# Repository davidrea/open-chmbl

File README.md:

# open-chmbl

In automotive engineering, the CHMBL is the "Center High-Mounted Brake Light" — this
repository is an **"Open-sourCe Helmet Mounted Brake Light"** for motorcyclists.

A battery-powered ~8″ LED bar worn on the rider's back — magnetically clamped to a
jacket or backpack — lights up when the motorcycle is braking. The reference bike
doesn't publish a brake-switch bit on its **CAN bus**, so braking is **inferred from
wheel-speed deceleration** read off the bus (via the Euro 5 diagnostic port,
**listen-only**) and sent wirelessly to the rider-side unit over **ESP-NOW**. Clutch
and gear/neutral context lets it hold the light through a stop and release it sensibly
when the bike pulls away — deriving deceleration from the bike's own CAN wheel-speed
(not an accelerometer) keeps it clear of the inertial-detection patents.

Two units, both ESP32-based:

- **[`transmitter/`](transmitter)** — bike-side; plugs into the diagnostic port,
  decodes CAN, broadcasts braking state.
- **[`brake_light/`](brake_light)** — rider-side; battery-powered LED bar (fabric
  mount this rev; helmet fitment deferred) that renders the state.

> ⚠️ Auxiliary device. It does **not** replace the bike's factory brake light, and
> helmet-mounted lighting is restricted in some places. Read
> **[`docs/safety-regulatory.md`](docs/safety-regulatory.md)** before building or
> riding.

## Start here

- **[`ARCHITECTURE.md`](ARCHITECTURE.md)** — system overview and design index.
- **[`docs/feature-functions.md`](docs/feature-functions.md)** — per-device capabilities.
- **[`docs/design/README.md`](docs/design/README.md)** — how we build it: design
  elements, implemented one at a time in isolation.
- [`docs/cli.md`](docs/cli.md) · [`docs/hardware.md`](docs/hardware.md) ·
  [`docs/firmware.md`](docs/firmware.md) · [`docs/protocol.md`](docs/protocol.md) ·
  [`docs/can-profiles.md`](docs/can-profiles.md) ·
  [`docs/safety-regulatory.md`](docs/safety-regulatory.md) ·
  [`docs/roadmap.md`](docs/roadmap.md)

Status: **architecture / design phase** (see the roadmap).

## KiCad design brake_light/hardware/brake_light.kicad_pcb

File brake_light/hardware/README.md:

# Brake_light — hardware

Rider-side electronics. See [`docs/hardware.md §2`](../../docs/hardware.md#2-brake_light-rider-side)
for the block diagram and parts sketch.

Key constraints:
- **Bare ESP32-C3 module** (ESP32-C3-WROOM-02 baseline) + **chip-down** LiIon
  charger, DC-DC, and LED driver. Moved off the integrated dev-board path (previously
  scoped in the removed `§2.1` module survey) to unlock the thin/wide form factor
  below — see [`docs/hardware.md §2.1`](../../docs/hardware.md#21-parts-direction-bare-module--chip-down).
- **~8″ wide red LED bar** (620–630 nm mid-power) driven from a boost constant-current
  driver. Series-string + boost topology set in
  [`docs/design/de-04`](../../docs/design/de-04-led-render.md), which down-selected the
  TI **LM3410**; the **first pass fitted two `AP3019AKTR` drivers** on the §3.1
  two-parallel-strings branch — see
  [the as-built summary below](#as-built-block-summary-first-pass-schematic) and
  [DE-04 §3.5](../../docs/design/de-04-led-render.md).
- **Binary on/off bar — brightness deferred.** The firmware drives each driver's
  `CTRL`/`EN` pin as a **static enable**, and the LED current is fixed by the sense
  resistors. No PWM dimming, no ambient auto-dimming for now; the decision is recorded
  in [`docs/design/de-04`](../../docs/design/de-04-led-render.md), the deferred element
  is [`de-02`](../../docs/design/de-02-auto-brightness.md). The ambient-light sensor is
  **fitted but unused**, so this is a firmware-only change later. Auto-dimming remains a
  safety requirement (no blinding at night) — deferred, not dropped.
- **Status-indicator LEDs** — **separate from the bar** for status/fault reporting
  ([`docs/design/de-10`](../../docs/design/de-10-status-indicator.md)). DE-10 specified a
  chip-down WS2812B; the **first pass fitted two discrete mono LEDs (D13 RED / D14 GRN)**
  instead, which loses the full RGB code space — see
  [DE-10 §3](../../docs/design/de-10-status-indicator.md).
- **Battery: 1S 18650 Li-ion, protected cell** + USB-C charging. 18650 chosen over
  pouch/LiPo because pouch cells need mechanical compression the thin enclosure can't
  provide; a protected cell means the charge IC doesn't have to double as cell
  protection. The charger baseline was an MCP73871 (load-share); the **first pass fitted
  a `BQ21040DBV`**, so the load-sharing behaviour needs confirming.
- **Form factor: thin, short-in-vertical (viewed from the rear), wide.** The ~8″ LED
  bar sets the width; the 18650's ~18 mm diameter sets the enclosure-thickness floor.
- **Mount: magnetic to jacket / backpack fabric.** Magnets live in the light
  assembly; a thin steel strip or washers sit inside the garment or pack so the
  fabric is sandwiched between them. This is the [garment / backpack shoulder
  mount](../../docs/design/explorations/mounting-magnetic.md#exploration-a--garment--backpack-shoulder-mount)
  exploration promoted to the current baseline; helmet fitment and cross-form
  interchangeability are **deferred**.
- Sized for a full-day runtime target — with a ~3000 mAh 18650 the runtime budget
  roughly doubles the earlier 1500 mAh LiPo worked example (see hardware doc).
- Sealed, IP65+ enclosure.

⚠️ Mounting + Li-ion safety are mandatory reading: [`docs/safety-regulatory.md`](../../docs/safety-regulatory.md).

---

## Status of the design files

| File | State |
|------|-------|
| [`brake_light.kicad_sch`](brake_light.kicad_sch) | **First pass, committed.** Power, charge, buck, USB-C + ESD, MCU, ambient-light sensor and both LED strings are drawn and wired. Four MCU-side nets are **not yet wired** — see [Not yet assigned](#not-yet-assigned-provisional-in-firmware). |
| [`brake_light.kicad_pcb`](brake_light.kicad_pcb) | **First pass, committed.** Carries the netlist generated from the schematic (used to verify the table below). Not yet fabricated or brought up. |
| BOM | To be exported once the unwired nets are resolved. |
| Enclosure / mount files | Still to be added (Phase 4). |

> Nothing here has been built or measured yet. Treat every value below as
> "as-drawn", not "as-measured".

## As-built block summary (first-pass schematic)

| Block | Part | Notes |
|-------|------|-------|
| MCU | **U1 `ESP32-C3-WROOM-02`** | Bare module; native USB on IO18/IO19 |
| Brake bar, string A | **U3 `AP3019AKTR`** boost CC driver | L1 22 µH, C4 0.22 µF out, **R4 560 mΩ** sense; drives **D3…D12 (10 emitters)** in series |
| Brake bar, string B | **U6 `AP3019AKTR`** boost CC driver | L2 22 µH, C7 0.22 µF out, **R10 560 mΩ** sense; drives **D15…D24 (10 emitters)** in series |
| Charger | **U2 `BQ21040DBV`** | From USB VBUS; `TS` ← NTC **TH1**, `ISET` ← R9, `~CHG` → status LED **D2** |
| 3V3 rail | **U7 `TPS62162DSGR`** buck | VBAT → 3V3; `EN` tied to VBAT (always on); `PG` → R14 1 kΩ → the C3's `EN`, so the MCU is held in reset until 3V3 is good |
| Ambient light | **U5 `ISL29035`** | I²C + interrupt. **Populated but unused in firmware** — see [DE-02](../../docs/design/de-02-auto-brightness.md) |
| USB-C | **J2** + **U4 `USBLC6-2P6`** | CC1/CC2 5.1 kΩ (R1/R2), D+/D− ESD-clamped |
| Status LEDs | **D13 (RED)**, **D14 (GRN)** | Each **cathode → GND, anode → 100 Ω (R21 / R20) → MCU pin**, i.e. **active high** |
| Buttons | **SW1 BOOT/USER**, **SW2 RST** | Both switch to GND (active low) |
| Cell | **BT1** 1S Li-ion (18650) | |

**Fixed LED current setpoint.** The sense resistors set the string current in
hardware — there is no firmware dimming (see
[DE-04](../../docs/design/de-04-led-render.md)). The schematic's own sizing note reads
`R = 0.2 V / I_LED`, so **R = 560 mΩ → I_string ≈ 357 mA**, dissipating ≈ 71 mW in the
sense resistor. Ten 620–630 nm emitters at V<sub>f</sub> ≈ 2.1 V put each string at
≈ 21 V, inside the driver's noted 30 V ceiling. The intensity this *should* be is set by
the [LED brightness benchmark](../../docs/led-brightness-benchmark.md) — which is still
the governing sizing study, and which this first pass has **not** been reconciled against
(see the open items below).

---

## Pin map

Derived from the committed design files: the ESP32-C3 pin numbers and the pin↔net
assignments below were read out of **`brake_light.kicad_sch`** and cross-checked against
the net assigned to each pad in **`brake_light.kicad_pcb`** (which KiCad generates from
the schematic). Where the two are quoted together they agree.

### Verified from the netlist

| Function | ESP32-C3 signal | Module pad | How it is wired |
|----------|-----------------|:----------:|-----------------|
| ISL29035 **SDA** | `IO0` | 18 | → U5.6 `SDA`; 4.7 kΩ pull-up (R6) to +3V3 |
| ISL29035 **SCL** | `IO1` | 17 | → U5.5 `SCL`; 4.7 kΩ pull-up (R7) to +3V3 |
| ISL29035 **INT** | `IO3` | 15 | → U5.4 `~INT`; 4.7 kΩ pull-up (R8) to +3V3 |
| **SW1** BOOT/USER button | `IO9` | 8 | → SW1.1; SW1.2 → GND ⇒ **active low**, needs the internal pull-up |
| USB **D−** | `IO18` | 13 | → U4 `I/O1` → J2 `A7`/`B7` |
| USB **D+** | `IO19` | 14 | → U4 `I/O2` → J2 `A6`/`B6` |
| UART **TXD** test point | `IO21` | 12 | → TP1 |
| UART **RXD** test point | `IO20` | 11 | → TP2 |
| Chip **reset** | `EN` | 2 | SW2 (RST) to GND + R5 10 kΩ pull-up + R14 from U7 `PG` |
| Supply | `3V3` / `GND` | 1 / 9, 19 | U7 buck output |

So the ambient-light sensor, the user button, USB and the console test points **are**
fully determined by the committed design files.

### Not yet assigned (provisional in firmware)

These four MCU-side nets are **not wired in the committed first pass** — the board
netlist reports each pad as its own single-pad `unconnected-(…)` net:

| Function | Pad that is open | Netlist name |
|----------|------------------|--------------|
| Brake bar **string A** driver enable | U3 pin 4 `CTRL` | `unconnected-(U3-CTRL-Pad4)` |
| Brake bar **string B** driver enable | U6 pin 4 `CTRL` | `unconnected-(U6-CTRL-Pad4)` |
| Status LED **RED** feed | R21 pin 1 (→ D13 anode) | `unconnected-(R21-Pad1)` |
| Status LED **GRN** feed | R20 pin 1 (→ D14 anode) | `unconnected-(R20-Pad1)` |

Free module GPIOs available for them: `IO2`, `IO4`, `IO5`, `IO6`, `IO7`, `IO8`, `IO10`.

The firmware therefore keeps all four as Kconfig symbols with **provisional defaults**,
so nothing is hard-coded ahead of a schematic review
([`brake_light/software/README.md`](../software/README.md)):

| Function | Provisional default (esp32c3) | Kconfig symbol |
|----------|-------------------------------|----------------|
| String A enable (U3 `CTRL`) | `IO5` | `CHMBL_BAR_EN_A_GPIO` |
| String B enable (U6 `CTRL`) | `IO6` | `CHMBL_BAR_EN_B_GPIO` |
| Status LED RED (D13 via R21) | `IO7` | `CHMBL_STATUS_LED_RED_GPIO` |
| Status LED GRN (D14 via R20) | `IO10` | `CHMBL_STATUS_LED_GRN_GPIO` |

Why those four, if the schematic review wants a starting point:

- **Avoid `IO2` and `IO8`** — both are ESP32-C3 boot **strapping** pins. A driver-enable
  or LED pin sitting low through reset would change the boot mode.
- **`IO9` is taken** by SW1 (and is itself the download-boot strap).
- **Keep `IO4` free.** With `IO0`/`IO1`/`IO3` on the I²C bus and `IO2` strapping, `IO4` is
  the last ADC1-capable pin left, and a battery-sense divider (DE-05) is the obvious next
  thing that needs one — note there is **no battery-voltage sense net on the board yet
  either**.
- `IO4`–`IO7` double as the C3's JTAG pins, which this board does not need: debug goes
  over the native USB Serial/JTAG on `IO18`/`IO19`.

**Active levels.** The status-LED orientation **is** verified (cathode to GND, anode fed
through the 100 Ω resistor), so those pins are **active high**. The AP3019A `CTRL` pin is
also active high, and the firmware drives it as a **static enable** — high = that string
lit at the sense-resistor setpoint, low = dark. That is a deliberate deferral of PWM
dimming, recorded in [DE-04](../../docs/design/de-04-led-render.md).

---

## Open items from this first pass

1. **Wire the four nets above** (both driver `CTRL` pins and both status-LED feeds), then
   fold the agreed GPIO numbers back into this table and the firmware's Kconfig defaults.
2. **Reconcile the LED operating point with the sizing study.** As drawn the bar is
   **2 strings × 10 emitters at ≈ 357 mA each** (≈ 714 mA of LED current). DE-04 §3.4's
   worked baseline is **one string of 8 at ≈ 80 mA**, sized to the
   [benchmark](../../docs/led-brightness-benchmark.md)'s ≈ 50–80 cd daylight target. The
   first-pass board is far above that, which matters more than usual now that brightness
   is fixed in hardware: with dimming deferred there is no firmware knob to pull it back.
   The sense resistors are the only adjustment.
3. **Driver part differs from the DE-04 down-select.** The board uses
   **`AP3019AKTR` ×2**; DE-04 §3.3's trade study concluded **TI LM3410**. The AP3019A's
   higher output ceiling (sheet note "MAX 30V") is what makes the 10-emitter strings
   possible, so this looks like a reasonable substitution — but it has not been run
   through the §3.3 criteria (V<sub>in</sub>-min against the 1S cutoff, switch current,
   EMI next to the 2.4 GHz radio). Confirm against the datasheet and record the outcome in
   DE-04.
4. **No battery-voltage sense and no MCU connection to the charger's `~CHG`** — battery
   state (DE-05) and the charge/low-battery status codes (DE-10) are not observable in
   firmware on this revision.
5. **ISL29035 is populated but unused.** Deliberate: it costs nothing to leave fitted and
   means no hardware change when [DE-02](../../docs/design/de-02-auto-brightness.md) is
   picked back up.

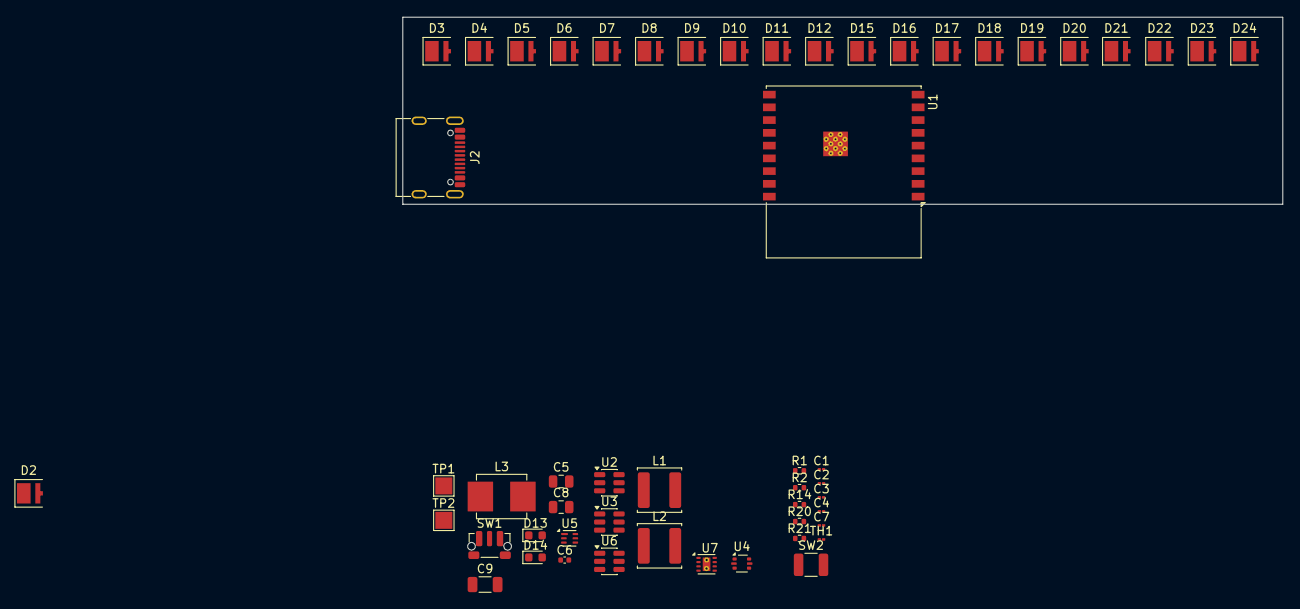
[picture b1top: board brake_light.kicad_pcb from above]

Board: 4 copper layers, 103.5 x 22.0 mm, 53 parts (0 on the bottom side), 45 nets, no tracks yet.

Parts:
C1, C2, C3: 1u; C_01005_0402Metric
C4, C7: 0.22u; C_01005_0402Metric
C5, C8: 10u; C_0805_2012Metric
C6: 100n; C_0402_1005Metric
C9: 22u; C_1206_3216Metric
D2, D3, D4, D5, D6, D7, D8, D9, D10, D11, D12, D15, D16, D17, D18, D19, D20, D21, D22, D23, D24: LED; LED_Luminus_MP-3030-1100_3.0x3.0mm
D13: RED; LED_0603_1608Metric
D14: GRN; LED_0603_1608Metric
J2: USB_C_Receptacle_USB2.0_14P; USB_C_Receptacle_G-Switch_GT-USB-7010ASV
L1, L2: 22u 1.1A; L_Sunlord_SWPA5020S
L3: 2.2u; L_Murata_LQH55DN_5.7x5.0mm
R1, R2: 5.1K; R_0402_1005Metric
R14: 1K; R_0402_1005Metric
R20, R21: 100; R_0402_1005Metric
SW1: BOOT/USER; SW_Push_1P1T-MP_NO_Horizontal_Alps_SKRTLAE010
SW2: RST; R_1210_3225Metric
TH1: Thermistor_NTC; R_01005_0402Metric
TP1: RX; TestPoint_Pad_2.0x2.0mm
TP2: TX; TestPoint_Pad_2.0x2.0mm
U1: ESP32-C3-WROOM-02
U2: BQ21040DBV; SOT-23-6
U3, U6: AP3019AKTR; SOT-23-6
U4: USBLC6-2P6; SOT-666
U5: ISL29035; Renesas_DFN-6_1.5x1.6mm_P0.5mm
U7: TPS62162DSGR; WSON-8-1EP_2x2mm_P0.5mm_EP0.9x1.6mm_ThermalVias

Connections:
+3.3V: C1.1, C5.1, C6.1, C9.1, L3.2, U1.1 (3V3), U5.1 (VDD), U7.6 (VOS)
+5VD: J2.A4 (VBUS), J2.A9 (VBUS), J2.B4 (VBUS), J2.B9 (VBUS), U2.6 (VIN), U4.5 (VBUS)
/DN: J2.A7 (D-), J2.B7 (D-), U1.13 (IO18), U4.1 (I/O1), U4.6 (I/O1)
/DP: J2.A6 (D+), J2.B6 (D+), U1.14 (IO19), U4.3 (I/O2), U4.4 (I/O2)
/EN: R14.1, SW2.1, U1.2 (EN)
/VBAT: C2.1, C3.1, C8.1, L1.2, L2.2, U2.2 (OUT), U3.6 (V_{IN}), U6.6 (V_{IN}), U7.2 (VIN), U7.3 (EN)
GND: C1.2, C2.2, C3.2, C4.2, C5.2, C6.2, C7.2, C8.2, C9.2, D13.1 (K), D14.1 (K), J2.A1 (GND), J2.A12 (GND), J2.B1 (GND), J2.B12 (GND), J2.SH (SHIELD), R1.2, R2.2, SW1.2, SW2.2, TH1.1, U1.9 (GND), U1.19 (GND), U2.5 (GND), U3.2 (GND), U4.2 (GND), U5.2 (GND), U6.2 (GND), U7.1 (PGND), U7.4 (AGND), U7.5 (FB), U7.9 (PAD)
unnamed: D2.1 (K), U2.3 (~CHG)
unnamed: C4.1, D3.2 (A), U3.5 (V_{OUT})
unnamed: D3.1 (K), D4.2 (A)
unnamed: D4.1 (K), D5.2 (A)
unnamed: D5.1 (K), D6.2 (A)
unnamed: D6.1 (K), D7.2 (A)
unnamed: D7.1 (K), D8.2 (A)
unnamed: D8.1 (K), D9.2 (A)
unnamed: D9.1 (K), D10.2 (A)
unnamed: D10.1 (K), D11.2 (A)
unnamed: D11.1 (K), D12.2 (A)
unnamed: D12.1 (K), U3.3 (FB)
unnamed: D13.2 (A), R21.2
unnamed: D14.2 (A), R20.2
unnamed: C7.1, D15.2 (A), U6.5 (V_{OUT})
unnamed: D15.1 (K), D16.2 (A)
unnamed: D16.1 (K), D17.2 (A)
unnamed: D17.1 (K), D18.2 (A)
unnamed: D18.1 (K), D19.2 (A)
unnamed: D19.1 (K), D20.2 (A)
unnamed: D20.1 (K), D21.2 (A)
unnamed: D21.1 (K), D22.2 (A)
unnamed: D22.1 (K), D23.2 (A)
unnamed: D23.1 (K), D24.2 (A)
unnamed: D24.1 (K), U6.3 (FB)
unnamed: J2.A5 (CC1), R1.1
unnamed: J2.B5 (CC2), R2.1
unnamed: U1.18 (IO0), U5.6 (SDA)
unnamed: U1.17 (IO1), U5.5 (SCL)
unnamed: U1.15 (IO3), U5.4 (~INT)
unnamed: SW1.1, U1.8 (IO9)
unnamed: TP2.1 (1_1), U1.11 (IO20/RXD)
unnamed: TP1.1 (1_1), U1.12 (IO21/TXD)
unnamed: TH1.2, U2.1 (TS)
unnamed: L1.1, U3.1 (SW)
unnamed: L2.1, U6.1 (SW)
unnamed: R14.2, U7.8 (PG)
unnamed: L3.1, U7.7 (SW)

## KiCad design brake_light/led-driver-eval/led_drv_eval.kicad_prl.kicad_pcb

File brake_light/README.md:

# Brake_light (rider-side)

Battery-powered ~8″ wide red LED bar worn on the rider's back — magnetically clamped
to a jacket or the top of a backpack between the shoulder blades (a steel strip or
washers inside the garment / pack completes the mount). Receives braking state from
the [`transmitter`](../transmitter) over [ESP-NOW](../docs/protocol.md) and renders
it on the bar, while managing its own 1S 18650 Li-ion battery, USB-C charging, pairing,
and [link-loss failsafe](../docs/protocol.md#4-failsafe--link-health).

The bar is driven as a **plain binary output** — on when braking, off otherwise, steady,
never flashing. **Brightness levels and ambient auto-dimming are deferred** (decision:
[`docs/design/de-04`](../docs/design/de-04-led-render.md); deferred element:
[`de-02`](../docs/design/de-02-auto-brightness.md)); the ambient-light sensor is on the
board but unread, so nothing has to change in hardware when it is picked back up.

Helmet fitment is **deferred** — the current form factor targets a thin, short-in-
the-vertical-axis, wide fabric-mounted bar so shell curvature and helmet-certification
questions don't gate the first build.

- [`hardware/`](hardware) — LED bar, 18650 + charging (chip-down), enclosure,
  magnetic fabric mount. A **first-pass schematic + PCB are committed** (not built yet);
  see the [pin map](hardware/README.md#pin-map).
- [`software/`](software) — ESP32-C3 firmware (ESP-NOW RX + binary brake-bar render).

⚠️ Mounting and battery safety are not optional — see
[`docs/safety-regulatory.md`](../docs/safety-regulatory.md). See
[`ARCHITECTURE.md`](../ARCHITECTURE.md) for the big picture.

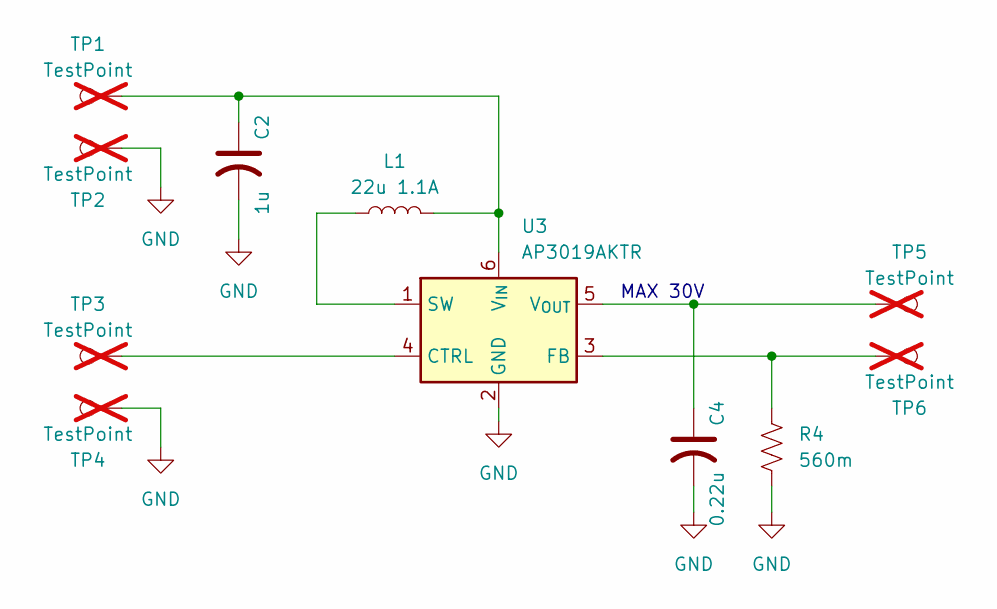
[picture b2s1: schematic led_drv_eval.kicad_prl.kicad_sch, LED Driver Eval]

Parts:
C2: 1u; C_0603_1608Metric; LCSC LMK107B7105KA-T
C4: 0.22u; C_0603_1608Metric; LCSC C107083
L1: 22u 1.1A; L_Sunlord_SWPA5020S; LCSC C96915
R4: 560m; R_1206_3216Metric; LCSC C5844413
TP1, TP2, TP3, TP4, TP5, TP6: TestPoint; TestPoint_Plated_Hole_D2.0mm; LCSC DNI; not fitted
U3: AP3019AKTR; SOT-23-6; LCSC C44956

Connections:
GND: C2.2, C4.2, R4.1, TP2.1 (1_1), TP4.1 (1_1), U3.2 (GND)
unnamed: TP3.1 (1_1), U3.4 (CTRL)
unnamed: R4.2, TP6.1 (1_1), U3.3 (FB)
unnamed: L1.1, U3.1 (SW)
unnamed: C2.1, L1.2, TP1.1 (1_1), U3.6 (V_{IN})
unnamed: C4.1, TP5.1 (1_1), U3.5 (V_{OUT})

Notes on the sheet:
MAX 30V

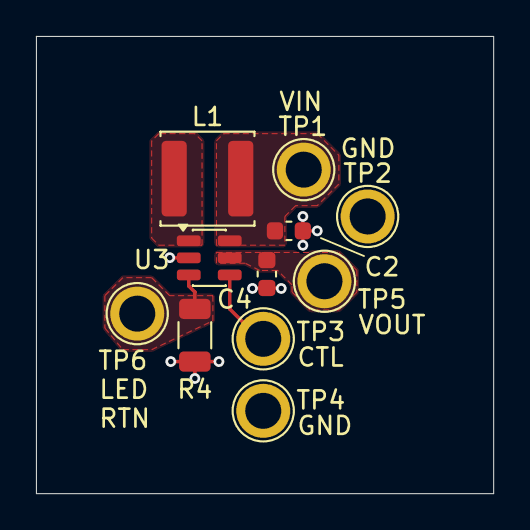
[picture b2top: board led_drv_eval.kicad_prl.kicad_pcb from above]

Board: 2 copper layers, 25.4 x 25.4 mm, 11 parts (0 on the bottom side), 6 nets.

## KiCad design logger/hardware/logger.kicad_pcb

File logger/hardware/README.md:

# Logger — hardware

Custom PCB (KiCad, [`logger.kicad_pro`](logger.kicad_pro)) that replaced the original
ESP-WROVER-KIT bring-up rig. Self-powered from the bike's 12 V or from USB-C, decodes
nothing on-board — it just timestamps and records **all** CAN traffic to a microSD card.
See [`../README.md`](../README.md) for the device-level description and
[`../software/README.md`](../software/README.md) for firmware status.

This board is also the **base design for the [`transmitter/`](../../transmitter)**
bike-side unit — see [§4](#4-shared-design-with-the-transmitter).

## 1. MCU: ESP32-S3-WROOM-1-N4

**ESP32-S3**, not the ESP32-C3 used elsewhere in this project (`brake_light/`, and
the transmitter's earlier sketch — see [`docs/hardware.md`](../../docs/hardware.md)).
The reason is the **microSD interface**: this design uses the SoC's native **SDMMC
host peripheral** (full 4-bit bus — `CLK`/`CMD`/`DAT0`–`DAT3`, see §3.4) for the
throughput a listen-only, no-filtering CAN capture needs. **The ESP32-C3 doesn't have
an SDMMC host peripheral** — only SPI — so it was not an option for this board. The
C3 stays the right choice for `brake_light/`, which has no SD card.

`-N4` = 4 MB flash, **no PSRAM**. (The retired ESP-WROVER-KIT target had 4 MB of
PSRAM the firmware currently depends on — `CONFIG_SPIRAM=y` — see the note in
[`../software/README.md`](../software/README.md).)

## 2. Power

```
 J3 pin 3 (+12 V, bike) ──▶ D4 (Schottky, reverse-pol.) ─┐
                                                          ├─▶ +5VD rail ─▶ U4 (TPS62172
 J2 (USB-C VBUS, 5 V)   ──▶ U3 (USBLC6-2P6 ESD) ─────────┘              buck) ─▶ +3V3
```

- **D4** (`20CJQ060`, Schottky) diode-ORs the bike's 12 V input against USB-C VBUS
  onto a shared **+5VD** rail, so the board can be bench-powered/flashed over USB-C
  without the bike connected, and the diode blocks backfeed onto the bike harness.
- **U4** (`TPS62172`, buck) steps +5VD down to **+3V3**, which powers the ESP32-S3,
  the CAN transceiver, and the microSD card.
- **D3** (`SM24CANB-02HTG`, dual TVS) sits right at J3 protecting CAN-H/CAN-L from
  bus transients.

There is no automotive load-dump-rated buck or a dedicated reverse-polarity FET here
(that was the original `docs/hardware.md` sketch) — this rev uses a Schottky diode for
reverse-polarity protection and a standard (not automotive-grade) buck. Revisit before
this board goes on a bike full-time; fine for bench/ride-logging use.

## 3. Connectors

| Ref | Type | Function |
|-----|------|----------|
| **J2** | USB-C receptacle | Power, flash, and console. **Native USB** — D+/D- wired directly to the ESP32-S3 (no USB-UART bridge chip). CC1/CC2 have 5.1 kΩ pull-downs (UFP power-sink detection). ESD-protected by U3 (`USBLC6-2P6`). |
| **J3** | JST-PH, 5-pin | Bike harness. Pin 1 **CAN-L**, pin 2 **CAN-H**, pin 3 **+12 V**, pin 4 **GND**, pin 5 **spare/unconnected**. TVS-protected at the connector (D3). |
| **J4** | JST-PH, 4-pin | Button/LED breakout. Pin 1 **GND**, pin 2 **LED drive** (through Q1, a low-side `2N7002K` switch), pin 3 **button input** (`BTN_SIG`, pulled up to 3V3, active-low), pin 4 **+3V3**. Both signal pins are TVS-protected (D1/D2, `PTVS3V3D1BALYL`) since this connector feeds an external panel-mount switch/LED on flying leads. |
| **J5** | microSD (Molex 104031-0811) | Full SDMMC **4-bit** bus (`CLK`, `CMD`, `DAT0`–`DAT3`) + card-detect (`DET_A`, pulled up) + 3V3/GND, wired straight to the ESP32-S3's SDMMC host peripheral. |

### 3.1 CAN transceiver

**U2 (`TCAN330`)**, 3.3 V logic — TXD/RXD to the ESP32-S3, plus its **silent-mode
(`S`) pin** wired to a GPIO so firmware can force RX-only operation in hardware, not
just in software. This pin was moved to a non-strapping GPIO to fix an earlier
strapping-pin conflict — see [§5](#5-resolved--can-silent-pin-moved-off-strapping-pin-gpio45).

### 3.2 microSD (J5)

Sized for a real ride-logging device: full 4-bit SDMMC, not the slower 1-bit/SPI
fallback. This is the peripheral that dictated the ESP32-S3 (§1).

### 3.3 Button/LED (J4)

Optional external start/stop button + status LED on flying leads (the onboard `SW1`/
`SW2` push-button footprints are DNI placeholders for a bench BOOT/EN header, not the
operator control). `Q1` (`2N7002K`) is a low-side switch for driving an LED through
J4 pin 2; `R4` is the current-limit resistor.

## 4. Shared design with the transmitter

The `transmitter/` bike-side unit reuses this exact board with **J4** (button/LED)
and **J5** (microSD) left unpopulated — the transmitter needs neither a card slot nor
a physical button/LED breakout. See
[`transmitter/hardware/README.md`](../../transmitter/hardware/README.md) and
[`docs/hardware.md §1`](../../docs/hardware.md#1-transmitter-bike-side).

## 5. Resolved — CAN silent pin moved off strapping pin (`GPIO45`)

An earlier rev routed the CAN transceiver's silent-mode pin (`U2` pin 8) to
**`GPIO45`**, one of the ESP32-S3's strapping pins — it selects the SPI-flash/PSRAM
supply voltage at reset (low = internal 3.3 V regulator, correct for this module;
high = expects an externally-supplied 1.8 V rail). **`R16`** pulls the `S` pin up to
3V3 to default the transceiver to **silent mode before firmware runs** (the right
failsafe for a listen-only device), but with `S` on `GPIO45` that pull-up also drove
the strapping pin high at boot — the same class of bug already hit once on this
project's bench boards (GPIO8 vs. the SPI-flash bus — see the blink-LED note) and a
known cause of ESP32-S3 boards that won't boot / report flash read errors.

**This is fixed in the current schematic:** the `S` pin is now on **`GPIO35`** (a
non-strapping GPIO, free on the `-N4` module since it has no PSRAM), and `R16` pulls
`GPIO35` up — keeping the default-silent failsafe without touching any strap.
`GPIO45` is left **unconnected**, so its internal pull-down selects the 3.3 V flash
supply as intended. The two other straps are clean too: `IO0` is the boot button
(internal pull-up) and `GPIO46` is unconnected. Still worth a bring-up confirmation
that `GPIO45` is unstuffed and boot is repeatable — see
[`BRINGUP.md §4`](BRINGUP.md#4-gpio--strapping-verification).

## 6. Fabrication / BOM

KiCad project only — `bom.csv`, `positions.csv`, `netlist.ipc`, and the JLC
export zip under `production/` are regenerated locally by the KiCad Fabrication
Toolkit plugin and are **gitignored**, not committed. Re-export from
[`logger.kicad_pcb`](logger.kicad_pcb) / [`logger.kicad_sch`](logger.kicad_sch) as
needed.

Key parts: `U1` ESP32-S3-WROOM-1-N4, `U2` TCAN330, `U4` TPS62172, `U3` USBLC6-2P6,
`D3` SM24CANB-02HTG, `D4` 20CJQ060.

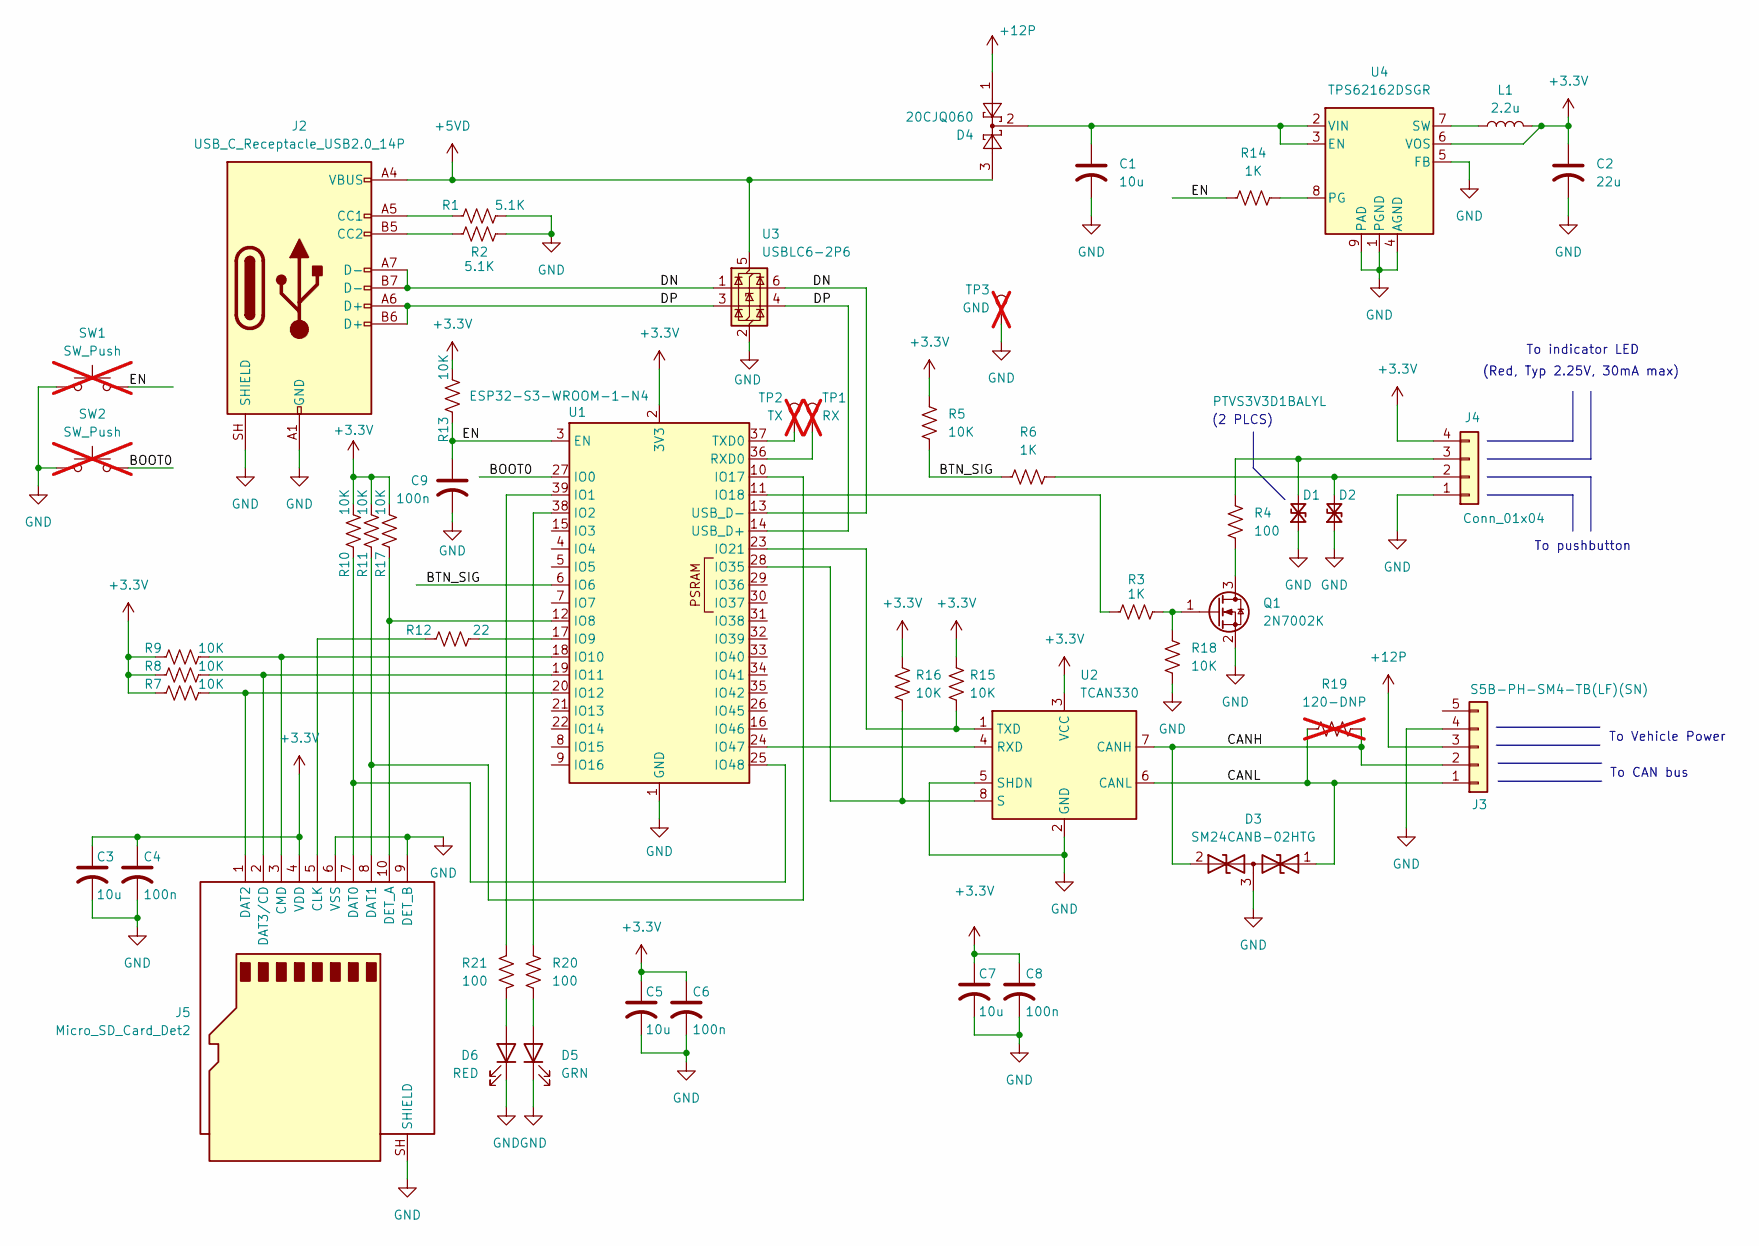
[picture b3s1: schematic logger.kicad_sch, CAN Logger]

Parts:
C1, C3, C5, C7: 10u; C_0805_2012Metric; LCSC C5677680
C2: 22u; C_1206_3216Metric; LCSC C91604
C4, C6, C8, C9: 100n; C_0402_1005Metric; LCSC C1525
D1, D2: PTVS3V3D1BALYL; D_SOD-882; LCSC C553419
D3: SM24CANB-02HTG; SOT-23; LCSC C151237
D4: 20CJQ060; SOT-223-3_TabPin2; LCSC C260229
D5: GRN; LED_0603_1608Metric; LCSC C125094
D6: RED; LED_0603_1608Metric; LCSC C94869
J2: USB_C_Receptacle_USB2.0_14P; USB_C_Receptacle_G-Switch_GT-USB-7010ASV; LCSC C2988369
J3: S5B-PH-SM4-TB(LF)(SN); JST_PH_S5B-PH-SM4-TB_1x05-1MP_P2.00mm_Horizontal; LCSC C265104
J4: Conn_01x04; JST_PH_S4B-PH-SM4-TB_1x04-1MP_P2.00mm_Horizontal; LCSC C265102
J5: Micro_SD_Card_Det2; microSD_HC_Molex_104031-0811; LCSC C585350
L1: 2.2u; L_Murata_LQH55DN_5.7x5.0mm; LCSC C701284
Q1: 2N7002K; SOT-23; LCSC C81445
R1, R2: 5.1K; R_0402_1005Metric; LCSC C105872
R3, R6, R14: 1K; R_0402_1005Metric; LCSC C106235
R4, R20, R21: 100; R_0402_1005Metric; LCSC C25076
R5, R7, R8, R9, R10, R11, R13, R15, R16, R17, R18: 10K; R_0402_1005Metric; LCSC C60490
R12: 22; R_0402_1005Metric; LCSC C114765
R19: 120-DNP; R_0402_1005Metric; LCSC DNI; not fitted
SW1, SW2: SW_Push; R_1210_3225Metric; LCSC DNI; not fitted
TP1: RX; TestPoint_Pad_2.0x2.0mm; LCSC DNI; not fitted
TP2: TX; TestPoint_Pad_2.0x2.0mm; LCSC DNI; not fitted
TP3: GND; TestPoint_Pad_2.0x2.0mm; LCSC DNI; not fitted
U1: ESP32-S3-WROOM-1-N4; ESP32-S3-WROOM-1; LCSC C2913197
U2: TCAN330; SOIC-8_3.9x4.9mm_P1.27mm; LCSC C2652876
U3: USBLC6-2P6; SOT-666; LCSC C15999
U4: TPS62162DSGR; WSON-8-1EP_2x2mm_P0.5mm_EP0.9x1.6mm_ThermalVias; LCSC C40256

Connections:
+3.3V: C2.1, C3.1, C4.1, C5.1, C6.1, C7.1, C8.1, J4.4, J5.4 (VDD), L1.2, R5.1, R7.1, R8.1, R9.1, R10.2, R11.2, R13.2, R15.1, R16.1, R17.2, U1.2 (3V3), U2.3 (VCC), U4.6 (VOS)
+5VD: D4.3, J2.A4 (VBUS), J2.A9 (VBUS), J2.B4 (VBUS), J2.B9 (VBUS), U3.5 (VBUS)
+12P: D4.1, J3.3
/BOOT0: SW2.2, U1.27 (IO0)
/BTN_SIG: R5.2, R6.1, U1.6 (IO6)
/CANH: D3.2 (A2), J3.2, R19.2, U2.7 (CANH)
/CANL: D3.1 (A1), J3.1, R19.1, U2.6 (CANL)
/DN: J2.A7 (D-), J2.B7 (D-), U1.13 (USB_D-), U3.1 (I/O1), U3.6 (I/O1)
/DP: J2.A6 (D+), J2.B6 (D+), U1.14 (USB_D+), U3.3 (I/O2), U3.4 (I/O2)
/EN: C9.1, R13.1, R14.1, SW1.2, U1.3 (EN)
GND: C1.2, C2.2, C3.2, C4.2, C5.2, C6.2, C7.2, C8.2, C9.2, D1.1 (A1), D2.1 (A1), D3.3 (common), D5.1 (K), D6.1 (K), J2.A1 (GND), J2.A12 (GND), J2.B1 (GND), J2.B12 (GND), J2.SH (SHIELD), J3.4, J4.1, J5.6 (VSS), J5.9 (DET_B), J5.SH (SHIELD), Q1.2 (S), R1.2, R2.2, R18.2, SW1.1, SW2.1, TP3.1 (1_1), U1.1 (GND), U1.40 (GND), U1.41 (GND), U2.2 (GND), U2.5 (SHDN), U3.2 (GND), U4.1 (PGND), U4.4 (AGND), U4.5 (FB), U4.9 (PAD)
unnamed: D1.2 (A2), J4.3, R4.1
unnamed: D2.2 (A2), J4.2, R6.2
unnamed: D5.2 (A), R20.2
unnamed: D6.2 (A), R21.2
unnamed: J2.A5 (CC1), R1.1
unnamed: J2.B5 (CC2), R2.1
unnamed: J5.5 (CLK), R12.1
unnamed: J5.3 (CMD), R9.2, U1.18 (IO10)
unnamed: J5.7 (DAT0), R10.1, U1.25 (IO48)
unnamed: J5.8 (DAT1), R11.1, U1.10 (IO17)
unnamed: J5.1 (DAT2), R7.2, U1.20 (IO12)
unnamed: J5.2 (DAT3/CD), R8.2, U1.19 (IO11)
unnamed: J5.10 (DET_A), R17.1, U1.12 (IO8)
unnamed: Q1.3 (D), R4.2
unnamed: Q1.1 (G), R3.2, R18.1
unnamed: R21.1, U1.39 (IO1)
unnamed: R20.1, U1.38 (IO2)
unnamed: R12.2, U1.17 (IO9)
unnamed: R3.1, U1.11 (IO18)
unnamed: R15.2, U1.23 (IO21), U2.1 (TXD)
unnamed: R16.2, U1.28 (IO35), U2.8 (S)
unnamed: U1.24 (IO47), U2.4 (RXD)
unnamed: TP1.1 (1_1), U1.36 (RXD0)
unnamed: TP2.1 (1_1), U1.37 (TXD0)
unnamed: C1.1, D4.2, U4.2 (VIN), U4.3 (EN)
unnamed: R14.2, U4.8 (PG)
unnamed: L1.1, U4.7 (SW)

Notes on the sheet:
To indicator LED
To Vehicle Power
To CAN bus
(2 PLCS)
(Red, Typ 2.25V, 30mA max)
To pushbutton

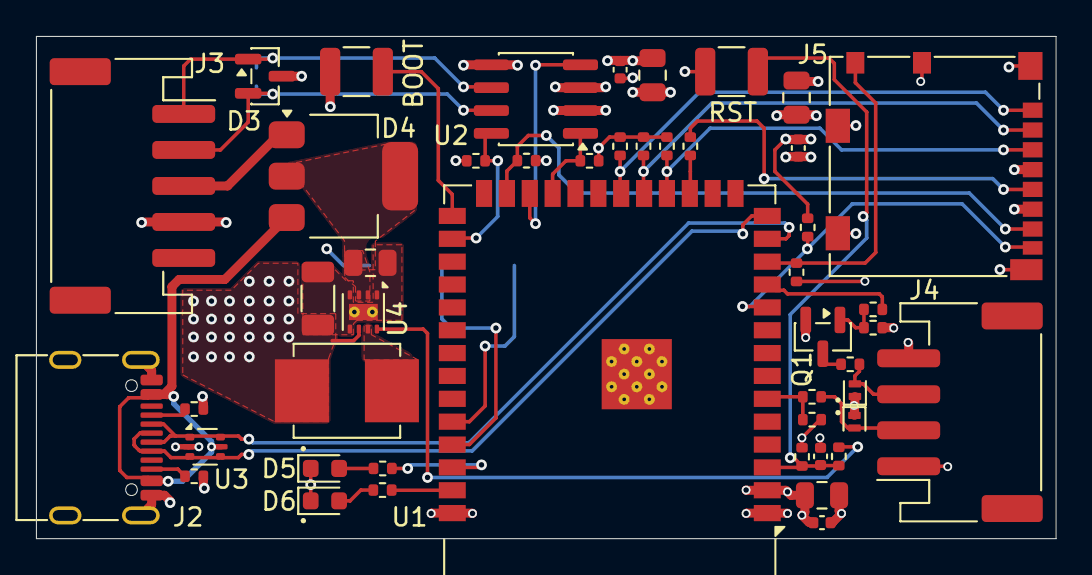
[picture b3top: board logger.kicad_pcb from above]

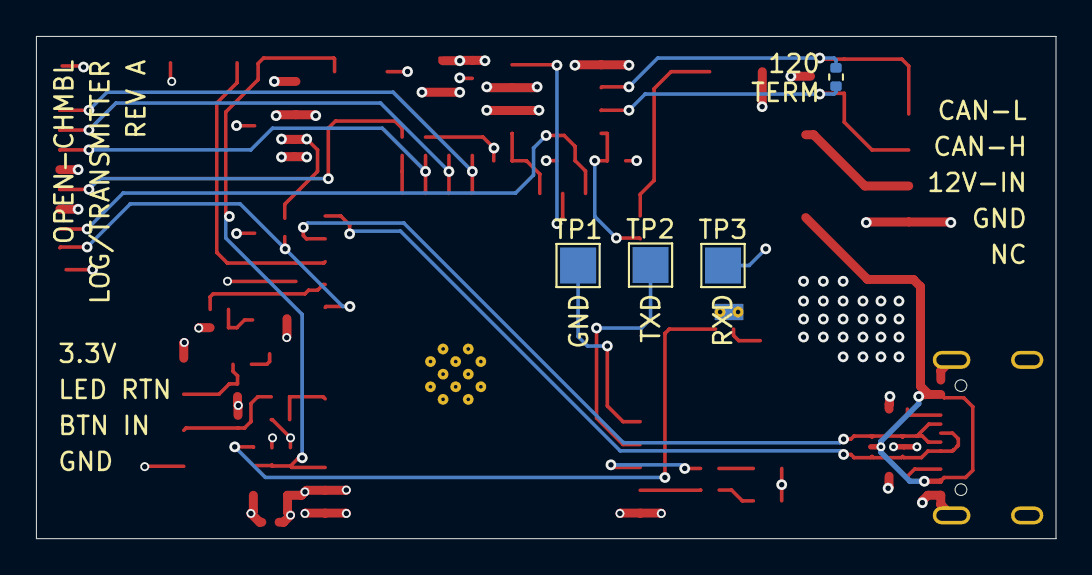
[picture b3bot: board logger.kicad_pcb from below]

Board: 4 copper layers, 56.6 x 27.9 mm, 51 parts (4 on the bottom side), 38 nets.

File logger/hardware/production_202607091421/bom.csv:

Designator,Footprint,Quantity,Value,LCSC Part #
"C1, C3, C5, C7",0805,4,10u,C5677680
C2,1206,1,22u,C91604
"C4, C6, C8, C9",0402,4,100n,C1525
"D1, D2",D_SOD-882,2,PTVS3V3D1BALYL,C553419
D3,SOT-23,1,SM24CANB-02HTG,C151237
D4,SOT-223-3_TabPin2,1,20CJQ060,C260229
J2,USB_C_Receptacle_G-Switch_GT-USB-7010ASV,1,USB_C_Receptacle_USB2.0_14P,C2988369
J3,JST_PH_S5B-PH-SM4-TB_1x05-1MP_P2.00mm_Horizontal,1,S5B-PH-SM4-TB(LF)(SN),C265104
J4,JST_PH_S4B-PH-SM4-TB_1x04-1MP_P2.00mm_Horizontal,1,Conn_01x04,C265102
J5,microSD_HC_Molex_104031-0811,1,Micro_SD_Card_Det2,C585350
L1,L_Murata_LQH55DN_5.7x5.0mm,1,2.2u,C701284
Q1,SOT-23,1,2N7002K,C81445
"R1, R2",0402,2,5.1K,C105872
"R10, R11, R13, R15, R16, R17, R18, R5, R7, R8, R9",0402,11,10K,C60490
R12,0402,1,22,C114765
"R14, R3, R6",0402,3,1K,C106235
R4,0402,1,47,C137973
U1,ESP32-S3-WROOM-1,1,ESP32-S3-WROOM-1-N8,C2913198
U2,SOIC-8_3.9x4.9mm_P1.27mm,1,TCAN330,C2652876
U3,SOT-666,1,USBLC6-2P6,C7519
U4,WSON-8-1EP_2x2mm_P0.5mm_EP0.9x1.6mm_ThermalVias,1,TPS62172DSG,C59873

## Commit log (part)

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2026-06-26 Tweaks mounting-magnetic.md
